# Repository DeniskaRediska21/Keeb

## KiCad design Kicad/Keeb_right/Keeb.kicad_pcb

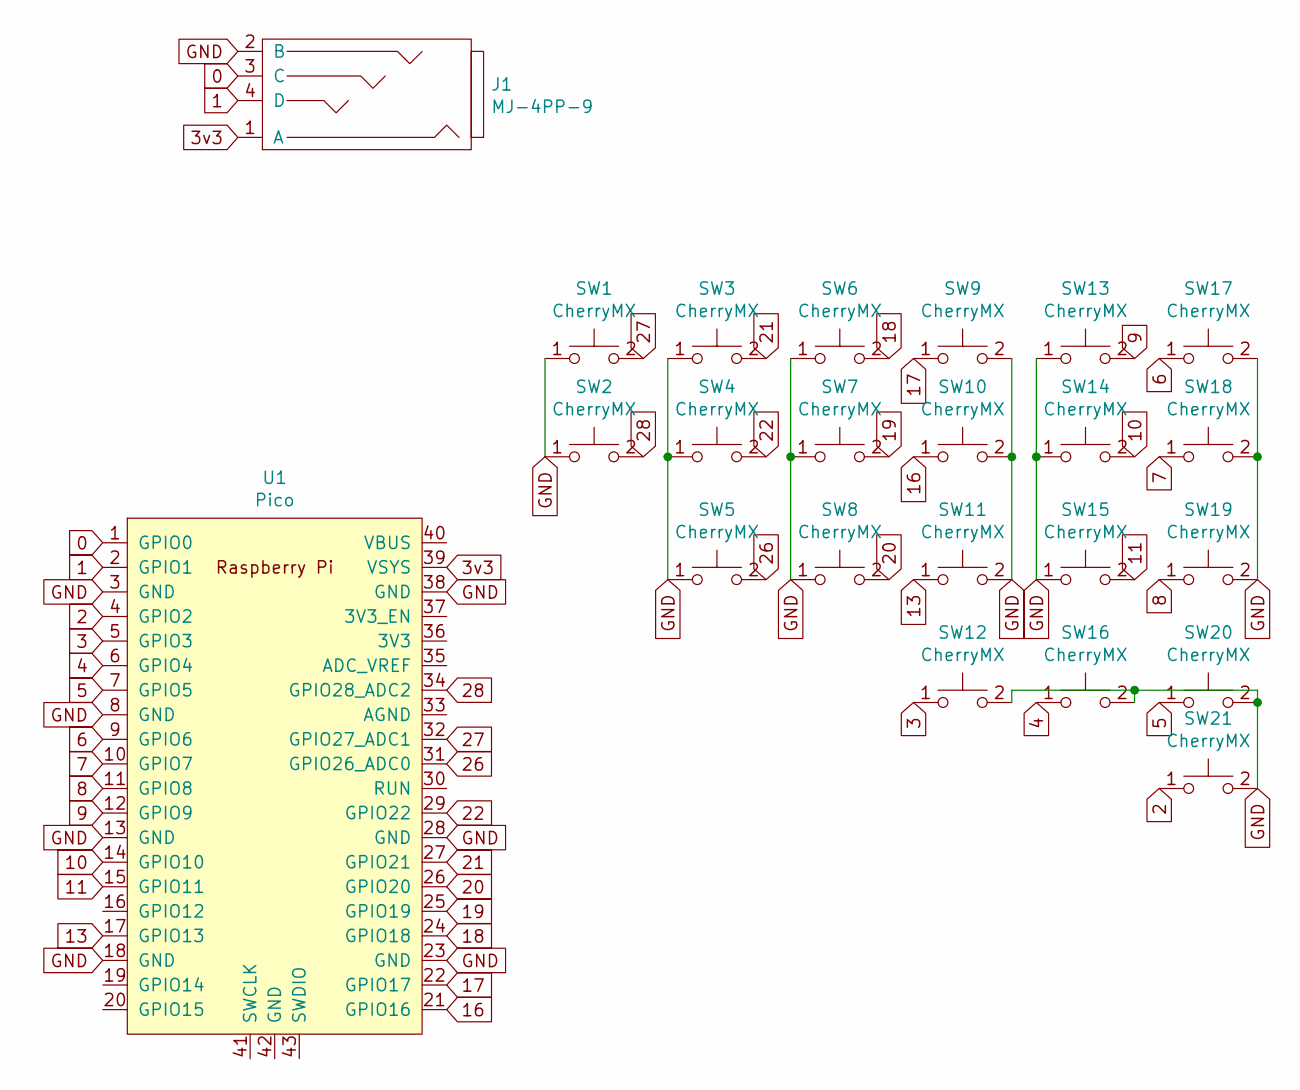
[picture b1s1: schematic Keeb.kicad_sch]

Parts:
J1: MJ-4PP-9
SW1, SW2, SW3, SW4, SW5, SW6, SW7, SW8, SW9, SW10, SW11, SW12, SW13, SW14, SW15, SW16, SW17, SW18, SW19, SW20, SW21: CherryMX; MX_PCB_1.00u
U1: Pico; RPi_Pico_SMD_TH

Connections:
0: J1.3 (C), U1.1 (GPIO0)
1: J1.4 (D), U1.2 (GPIO1)
2: SW21.1, U1.4 (GPIO2)
3: SW12.1, U1.5 (GPIO3)
3v3: J1.1 (A), U1.39 (VSYS)
4: SW16.1, U1.6 (GPIO4)
5: SW20.1, U1.7 (GPIO5)
6: SW17.1, U1.9 (GPIO6)
7: SW18.1, U1.10 (GPIO7)
8: SW19.1, U1.11 (GPIO8)
9: SW13.2, U1.12 (GPIO9)
10: SW14.2, U1.14 (GPIO10)
11: SW15.2, U1.15 (GPIO11)
13: SW11.1, U1.17 (GPIO13)
16: SW10.1, U1.21 (GPIO16)
17: SW9.1, U1.22 (GPIO17)
18: SW6.2, U1.24 (GPIO18)
19: SW7.2, U1.25 (GPIO19)
20: SW8.2, U1.26 (GPIO20)
21: SW3.2, U1.27 (GPIO21)
22: SW4.2, U1.29 (GPIO22)
26: SW5.2, U1.31 (GPIO26_ADC0)
27: SW1.2, U1.32 (GPIO27_ADC1)
28: SW2.2, U1.34 (GPIO28_ADC2)
GND: J1.2 (B), SW1.1, SW2.1, SW3.1, SW4.1, SW5.1, SW6.1, SW7.1, SW8.1, SW9.2, SW10.2, SW11.2, SW12.2, SW13.1, SW14.1, SW15.1, SW16.2, SW17.2, SW18.2, SW19.2, SW20.2, SW21.2, U1.3 (GND), U1.8 (GND), U1.13 (GND), U1.18 (GND), U1.23 (GND), U1.28 (GND), U1.38 (GND)

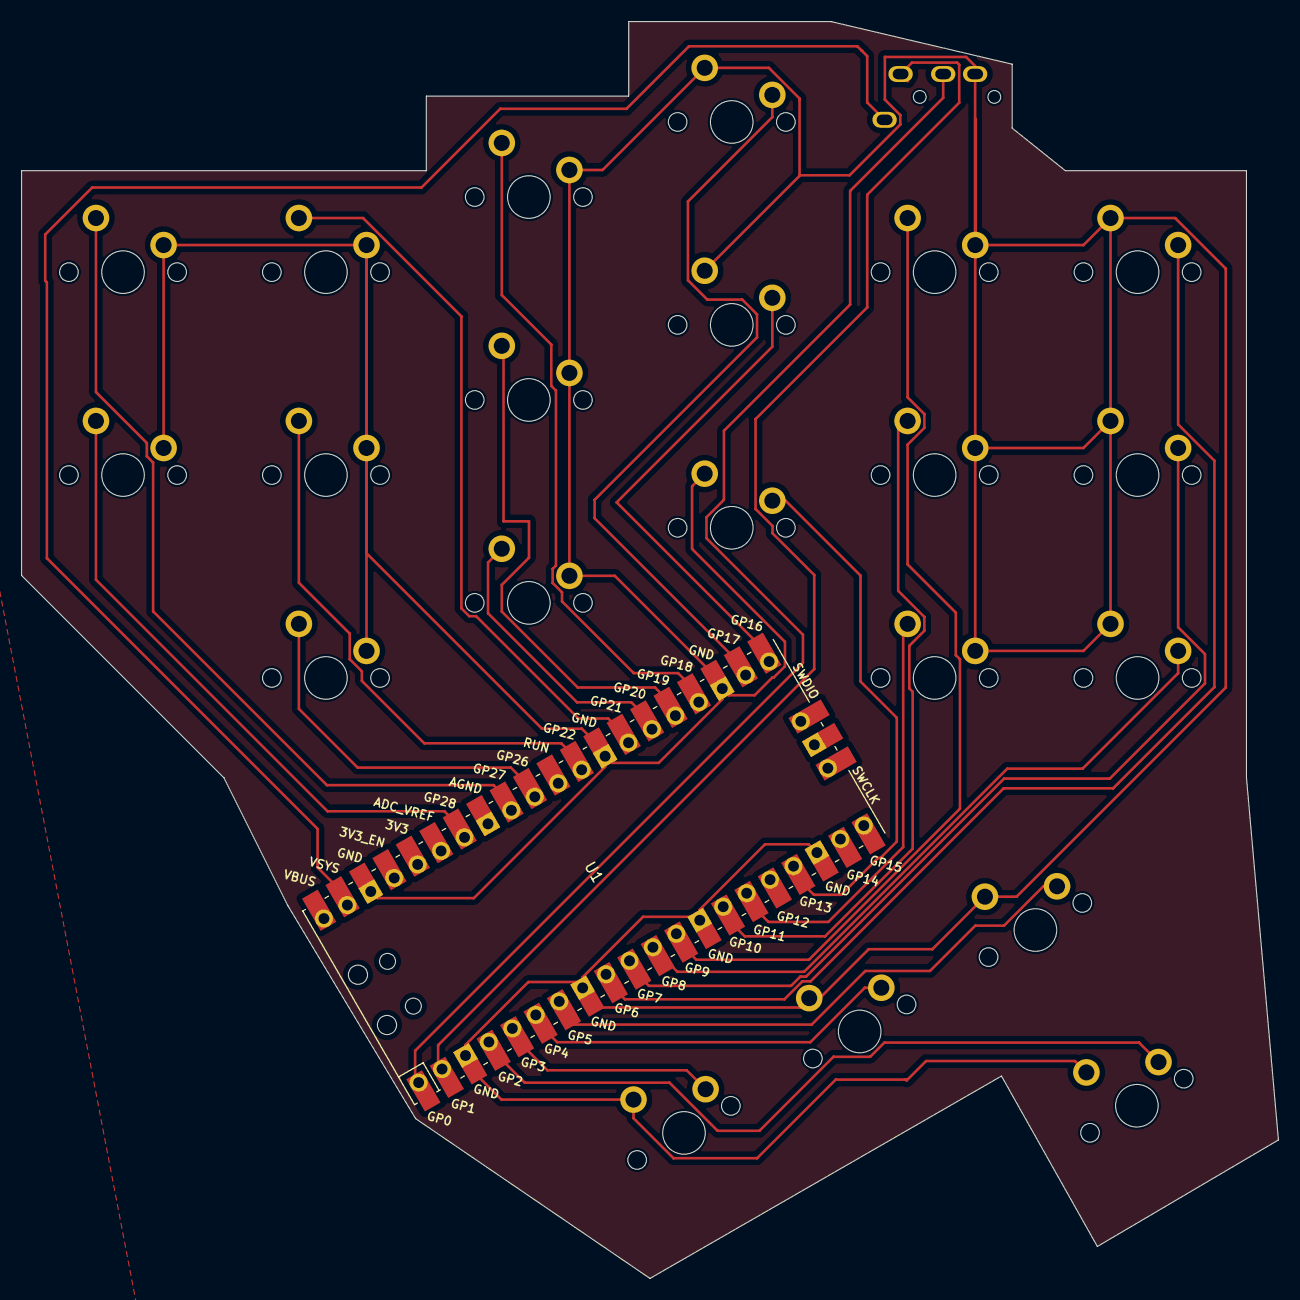
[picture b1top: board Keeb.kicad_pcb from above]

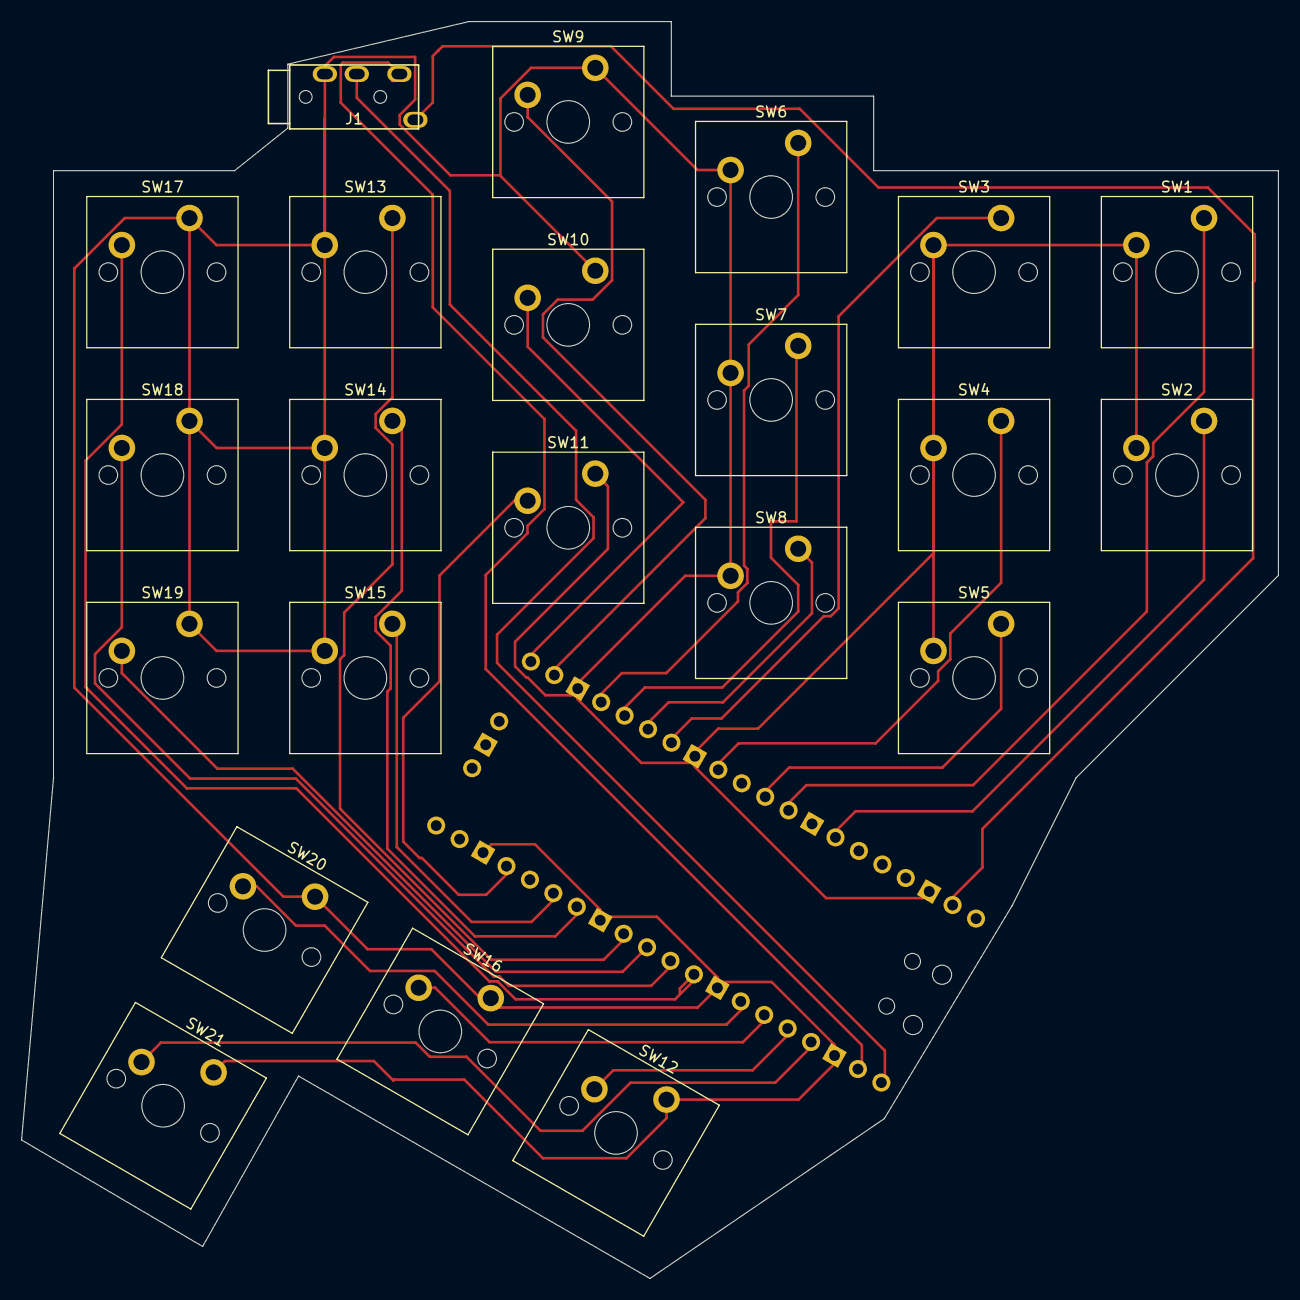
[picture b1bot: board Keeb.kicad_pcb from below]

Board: 2 copper layers, 118.0 x 118.0 mm, 23 parts (22 on the bottom side), 25 nets.

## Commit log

2023-10-25 Moved files around
2023-10-25 Sorted things into folders, finisher right and left halves
2023-10-27 spaced out tracks
2023-10-28 progressed on preparation for lasering
2023-11-25 soft
